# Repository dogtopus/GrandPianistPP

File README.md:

# GrandPianist++

Unofficial mods for SEGA Toys® Grand Pianist™ that aims for full MIDI playback, custom soundfonts and more.

(Heavily WIP and not ready for use yet.)

## More information

- [Reverse engineering notes](https://gist.github.com/dogtopus/aaefed8545139b112a3cba768b7c7403)

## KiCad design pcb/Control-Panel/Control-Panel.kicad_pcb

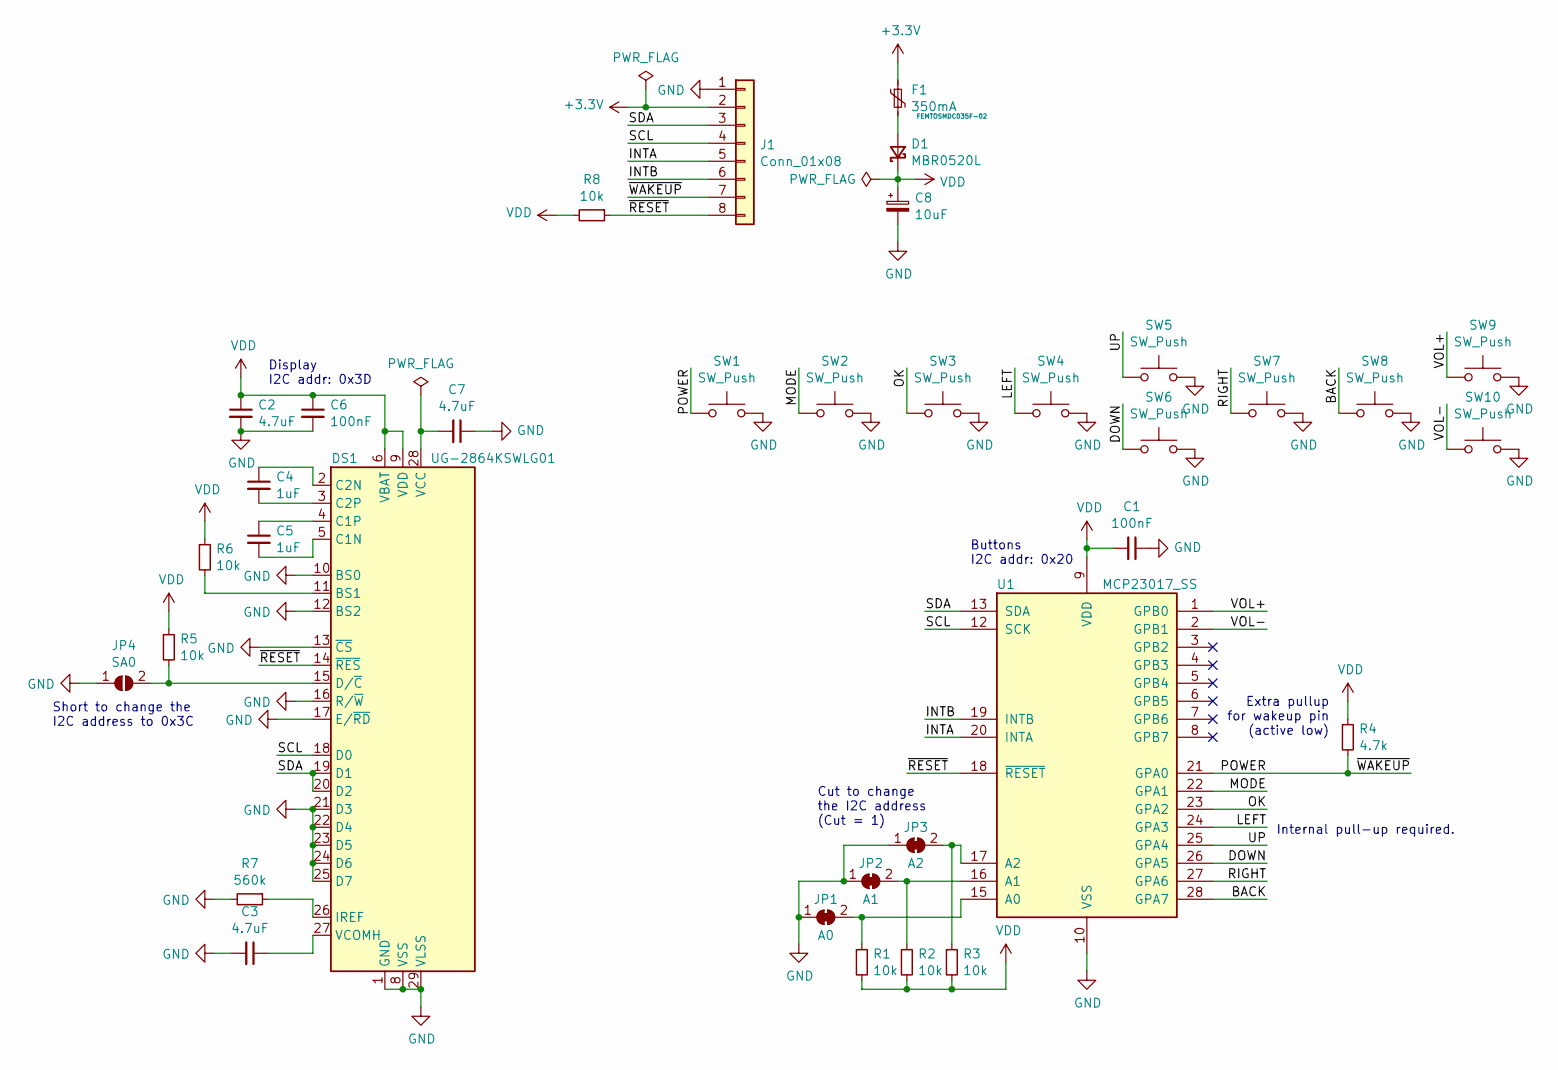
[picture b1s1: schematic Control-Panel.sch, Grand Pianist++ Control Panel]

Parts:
C1, C6: 100nF; C_0603_1608Metric
C2, C3, C7: 4.7uF; C_0603_1608Metric
C4, C5: 1uF; C_0603_1608Metric
C8: 10uF; CP_EIA-3216-18_Kemet-A
D1: MBR0520L; D_SOD-123
DS1: UG-2864KSWLG01; OLED-128O064D
F1: 350mA; Fuse_0603_1608Metric_Castellated; MPN FEMTOSMDC035F-02
J1: Conn_01x08; JST_PH_S8B-PH-SM4-TB_1x08-1MP_P2.00mm_Horizontal
JP1: A0; SolderJumper-2_P1.3mm_Bridged_RoundedPad1.0x1.5mm
JP2: A1; SolderJumper-2_P1.3mm_Bridged_RoundedPad1.0x1.5mm
JP3: A2; SolderJumper-2_P1.3mm_Bridged_RoundedPad1.0x1.5mm
JP4: SA0; SolderJumper-2_P1.3mm_Open_RoundedPad1.0x1.5mm
R1, R2, R3, R5, R6, R8: 10k; R_0603_1608Metric
R4: 4.7k; R_0603_1608Metric
R7: 560k; R_0603_1608Metric
SW1, SW2, SW3, SW4, SW5, SW6, SW7, SW8, SW9, SW10: SW_Push; MembraneButton_GrandPianist
U1: MCP23017_SS; SSOP-28_5.3x10.2mm_P0.65mm

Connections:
+3V3: F1.1, J1.2
/BACK: SW8.1, U1.28 (GPA7)
/DOWN: SW6.1, U1.26 (GPA5)
/INTA: J1.5, U1.20 (INTA)
/INTB: J1.6, U1.19 (INTB)
/LEFT: SW4.1, U1.24 (GPA3)
/MODE: SW2.1, U1.22 (GPA1)
/OK: SW3.1, U1.23 (GPA2)
/POWER: J1.7, R4.2, SW1.1, U1.21 (GPA0)
/RIGHT: SW7.1, U1.27 (GPA6)
/SCL: DS1.18 (D0), J1.4, U1.12 (SCK)
/SDA: DS1.19 (D1), DS1.20 (D2), J1.3, U1.13 (SDA)
/UP: SW5.1, U1.25 (GPA4)
/VOL+: SW9.1, U1.1 (GPB0)
/VOL-: SW10.1, U1.2 (GPB1)
/~RESET: DS1.14 (~RES), J1.8, R8.1, U1.18 (~RESET~)
GND: C1.1, C2.2, C3.2, C6.2, C7.1, C8.2, DS1.1 (GND), DS1.8 (VSS), DS1.10 (BS0), DS1.12 (BS2), DS1.13 (~CS), DS1.16 (R/~W), DS1.17 (E/~RD), DS1.21 (D3), DS1.22 (D4), DS1.23 (D5), DS1.24 (D6), DS1.25 (D7), DS1.29 (VLSS), DS1.30 (GND), J1.1, JP1.1 (A), JP2.1 (A), JP3.1 (A), JP4.1 (A), R7.2, SW1.2, SW2.2, SW3.2, SW4.2, SW5.2, SW6.2, SW7.2, SW8.2, SW9.2, SW10.2, U1.10 (VSS)
unnamed: C3.1, DS1.27 (VCOMH)
unnamed: C4.1, DS1.2 (C2N)
unnamed: C4.2, DS1.3 (C2P)
unnamed: C5.1, DS1.4 (C1P)
unnamed: C5.2, DS1.5 (C1N)
unnamed: C7.2, DS1.28 (VCC)
unnamed: D1.2 (A), F1.2
unnamed: DS1.11 (BS1), R6.2
unnamed: DS1.15 (D/~C), JP4.2 (B), R5.2
unnamed: DS1.26 (IREF), R7.1
unnamed: JP1.2 (B), R1.1, U1.15 (A0)
unnamed: JP2.2 (B), R2.1, U1.16 (A1)
unnamed: JP3.2 (B), R3.1, U1.17 (A2)
VDD: C1.2, C2.1, C6.1, C8.1, D1.1 (K), DS1.6 (VBAT), DS1.9 (VDD), R1.2, R2.2, R3.2, R4.1, R5.1, R6.1, R8.2, U1.9 (VDD)

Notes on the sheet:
Extra pullup for wakeup pin (active low)
Display I2C addr: 0x3D
Short to change the I2C address to 0x3C
Buttons I2C addr: 0x20
Internal pull-up required.
Cut to change the I2C address (Cut = 1)

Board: 2 copper layers, 35 parts (23 on the bottom side), 31 nets, no tracks yet.

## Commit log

2021-06-30 Add license and README.
2021-07-04 Critical mechanical parts placement.
